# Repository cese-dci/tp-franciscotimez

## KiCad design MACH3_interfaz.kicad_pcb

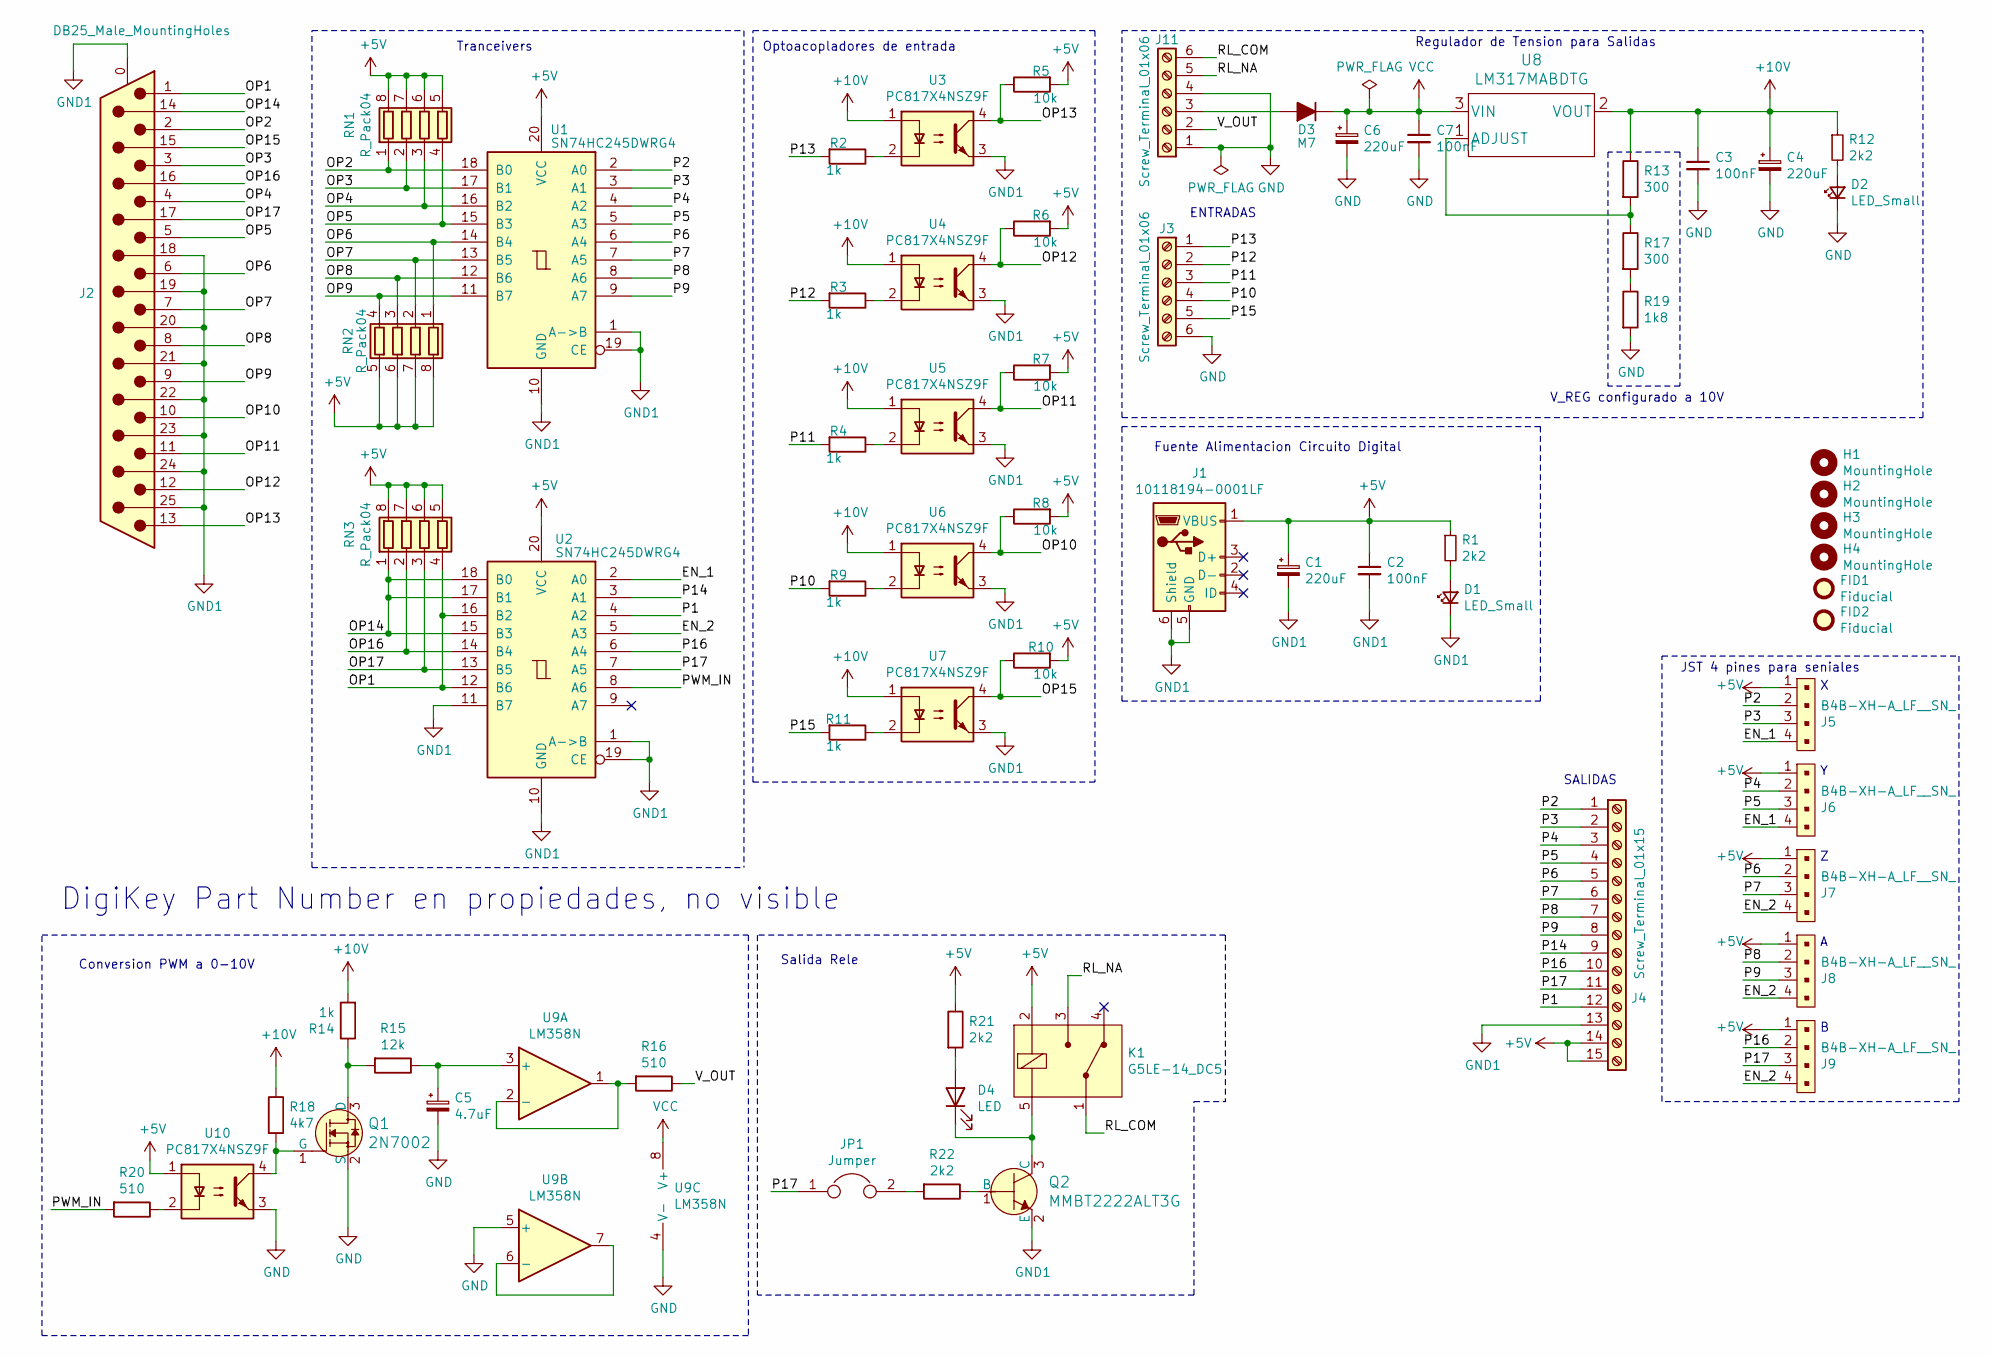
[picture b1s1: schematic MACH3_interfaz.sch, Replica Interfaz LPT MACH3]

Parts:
C1, C4: 220uF; CP_Radial_D6.3mm_P2.50mm
C2, C3, C7: 100nF; C_0805_2012Metric_Pad1.18x1.45mm_HandSolder
C5: 4.7uF; CP_Radial_D5.0mm_P2.00mm
C6: 220uF; CP_Radial_D8.0mm_P3.80mm
D1, D2: LED_Small; LED_0805_2012Metric_Pad1.15x1.40mm_HandSolder
D3: M7; D_SMA_Handsoldering
D4: LED; LED_0805_2012Metric_Pad1.15x1.40mm_HandSolder
FID1, FID2: Fiducial; Fiducial_1mm_Mask3mm
H1, H2, H3, H4: MountingHole; MountingHole_3.2mm_M3
J1: 10118194-0001LF; USB_Micro-B_Amphenol_10118194_Horizontal; DigiKey 609-4618-2-ND - Tape & Reel (TR)
J2: DB25_Male_MountingHoles; DSUB-25_Male_Horizontal_P2.77x2.84mm_EdgePinOffset4.94mm_Ho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
J3, J11: Screw_Terminal_01x06; TerminalBlock_Phoenix_MKDS-1,5-6_1x06_P5.00mm_Horizontal
J4: Screw_Terminal_01x15; TerminalBlock_Phoenix_MKDS-1,5-15_1x15_P5.00mm_Horizontal
J5, J6, J7, J8, J9: B4B-XH-A_LF__SN_; PinHeader_1x4_P2.5mm_Drill1.1mm; MPN B4B-XH-A(LF)(SN); Digi-Key_PN 455-2249-ND
JP1: Jumper; TestPoint_2Pads_Pitch2.54mm_Drill0.8mm
K1: G5LE-14_DC5; Relay_THT_G5LE-14; MPN G5LE-14 DC5; Digi-Key_PN Z1011-ND
Q1: 2N7002; SOT-23-3; MPN 2N7002; Digi-Key_PN 2N7002NCT-ND
Q2: MMBT2222ALT3G; SOT-23-3; MPN MMBT2222ALT3G; Digi-Key_PN MMBT2222ALT3GOSCT-ND
R1, R12, R21, R22: 2k2; R_0805_2012Metric_Pad1.20x1.40mm_HandSolder
R2, R3, R4, R9, R11, R14: 1k; R_0805_2012Metric_Pad1.20x1.40mm_HandSolder
R5, R6, R7, R8, R10: 10k; R_0805_2012Metric_Pad1.20x1.40mm_HandSolder
R13, R17: 300; R_0805_2012Metric_Pad1.20x1.40mm_HandSolder
R15: 12k; R_0805_2012Metric_Pad1.20x1.40mm_HandSolder
R16, R20: 510; R_0805_2012Metric_Pad1.20x1.40mm_HandSolder
R18: 4k7; R_0805_2012Metric_Pad1.20x1.40mm_HandSolder
R19: 1k8; R_0805_2012Metric_Pad1.20x1.40mm_HandSolder
RN1, RN2, RN3: R_Pack04; R_Array_Convex_4x1206
U1, U2: SN74HC245DWRG4; SO-20_12.8x7.5mm_P1.27mm; DigiKey 296-52721-2-ND - Tape & Reel (TR)
U3, U4, U5, U6, U7, U10: PC817X4NSZ9F; DIP-4_W7.62mm; DigiKey PC817X4NSZ9F-ND
U8: LM317MABDTG; TO-252-3_TabPin2; DigiKey LM317MABDTG-ND
U9: LM358N; SOIC-8_3.9x4.9mm_P1.27mm; DigiKey 2156-LM358N-ND

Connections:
+5V: C1.1, C2.1, J1.1 (VBUS), J4.14, J4.15, J5.1, J6.1, J7.1, J8.1, J9.1, K1.2 (COIL), R1.1, R5.2, R6.2, R7.2, R8.2, R10.2, R21.1, RN1.5 (R4.2), RN1.6 (R3.2), RN1.7 (R2.2), RN1.8 (R1.2), RN2.5 (R4.2), RN2.6 (R3.2), RN2.7 (R2.2), RN2.8 (R1.2), RN3.5 (R4.2), RN3.6 (R3.2), RN3.7 (R2.2), RN3.8 (R1.2), U1.20 (VCC), U2.20 (VCC), U10.1
+10V: C3.1, C4.1, R12.1, R13.1, R14.2, R18.1, U3.1, U4.1, U5.1, U6.1, U7.1, U8.2 (VOUT)
/EN_1: J5.4, J6.4, U2.2 (A0)
/EN_2: J7.4, J8.4, J9.4, U2.5 (A3)
/OP1: J2.1, RN3.4 (R4.1), U2.12 (B6), U2.16 (B2)
/OP2: J2.2, RN1.1 (R1.1), U1.18 (B0)
/OP3: J2.3, RN1.2 (R2.1), U1.17 (B1)
/OP4: J2.4, RN1.3 (R3.1), U1.16 (B2)
/OP5: J2.5, RN1.4 (R4.1), U1.15 (B3)
/OP6: J2.6, RN2.1 (R1.1), U1.14 (B4)
/OP7: J2.7, RN2.2 (R2.1), U1.13 (B5)
/OP8: J2.8, RN2.3 (R3.1), U1.12 (B6)
/OP9: J2.9, RN2.4 (R4.1), U1.11 (B7)
/OP10: J2.10, R8.1, U6.4
/OP11: J2.11, R7.1, U5.4
/OP12: J2.12, R6.1, U4.4
/OP13: J2.13, R5.1, U3.4
/OP14: J2.14, RN3.1 (R1.1), U2.15 (B3), U2.17 (B1), U2.18 (B0)
/OP15: J2.15, R10.1, U7.4
/OP16: J2.16, RN3.2 (R2.1), U2.14 (B4)
/OP17: J2.17, RN3.3 (R3.1), U2.13 (B5)
/P1: J4.12, U2.4 (A2)
/P2: J4.1, J5.2, U1.2 (A0)
/P3: J4.2, J5.3, U1.3 (A1)
/P4: J4.3, J6.2, U1.4 (A2)
/P5: J4.4, J6.3, U1.5 (A3)
/P6: J4.5, J7.2, U1.6 (A4)
/P7: J4.6, J7.3, U1.7 (A5)
/P8: J4.7, J8.2, U1.8 (A6)
/P9: J4.8, J8.3, U1.9 (A7)
/P10: J3.4, R9.2
/P11: J3.3, R4.2
/P12: J3.2, R3.2
/P13: J3.1, R2.2
/P14: J4.9, U2.3 (A1)
/P15: J3.5, R11.2
/P16: J4.10, J9.2, U2.6 (A4)
/P17: J4.11, J9.3, JP1.1, U2.7 (A5)
/PWM_IN: R20.2, U2.8 (A6)
/RL_COM: J11.6, K1.1 (COM)
/RL_NA: J11.5, K1.3 (NO)
/V_OUT: J11.2, R16.1
GND: C3.2, C4.2, C5.2, C6.2, C7.2, D2.1 (K), J3.6, J11.1, J11.4, Q1.2 (S), R19.2, U9.4 (V-), U9.5 (+), U10.3
GND1: C1.2, C2.2, D1.1 (K), J1.5 (GND), J1.6 (Shield), J2.0 (PAD), J2.18, J2.19, J2.20, J2.21, J2.22, J2.23, J2.24, J2.25, J4.13, Q2.2 (E), U1.1 (A->B), U1.10 (GND), U1.19 (CE), U2.1 (A->B), U2.10 (GND), U2.11 (B7), U2.19 (CE), U3.3, U4.3, U5.3, U6.3, U7.3
unnamed: C5.1, R15.1, U9.3 (+)
unnamed: D1.2 (A), R1.2
unnamed: D2.2 (A), R12.2
unnamed: D3.2 (A), J11.3
unnamed: D4.1 (K), K1.5 (COIL), Q2.3 (C)
unnamed: D4.2 (A), R21.2
unnamed: JP1.2, R22.2
unnamed: Q1.1 (G), R18.2, U10.4
unnamed: Q1.3 (D), R14.1, R15.2
unnamed: Q2.1 (B), R22.1
unnamed: R2.1, U3.2
unnamed: R3.1, U4.2
unnamed: R4.1, U5.2
unnamed: R9.1, U6.2
unnamed: R11.1, U7.2
unnamed: R13.2, R17.1, U8.1 (ADJUST)
unnamed: R16.2, U9.1, U9.2 (-)
unnamed: R17.2, R19.1
unnamed: R20.1, U10.2
unnamed: U9.6 (-), U9.7
VCC: C6.1, C7.1, D3.1 (K), U8.3 (VIN), U9.8 (V+)

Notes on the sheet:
ENTRADAS
SALIDAS
V_REG configurado a 10V
Fuente Alimentacion Circuito Digital
Regulador de Tension para Salidas
Salida Rele
Conversion PWM a 0-10V
Optoacopladores de entrada
Tranceivers
JST 4 pines para seniales
DigiKey Part Number en propiedades, no visible

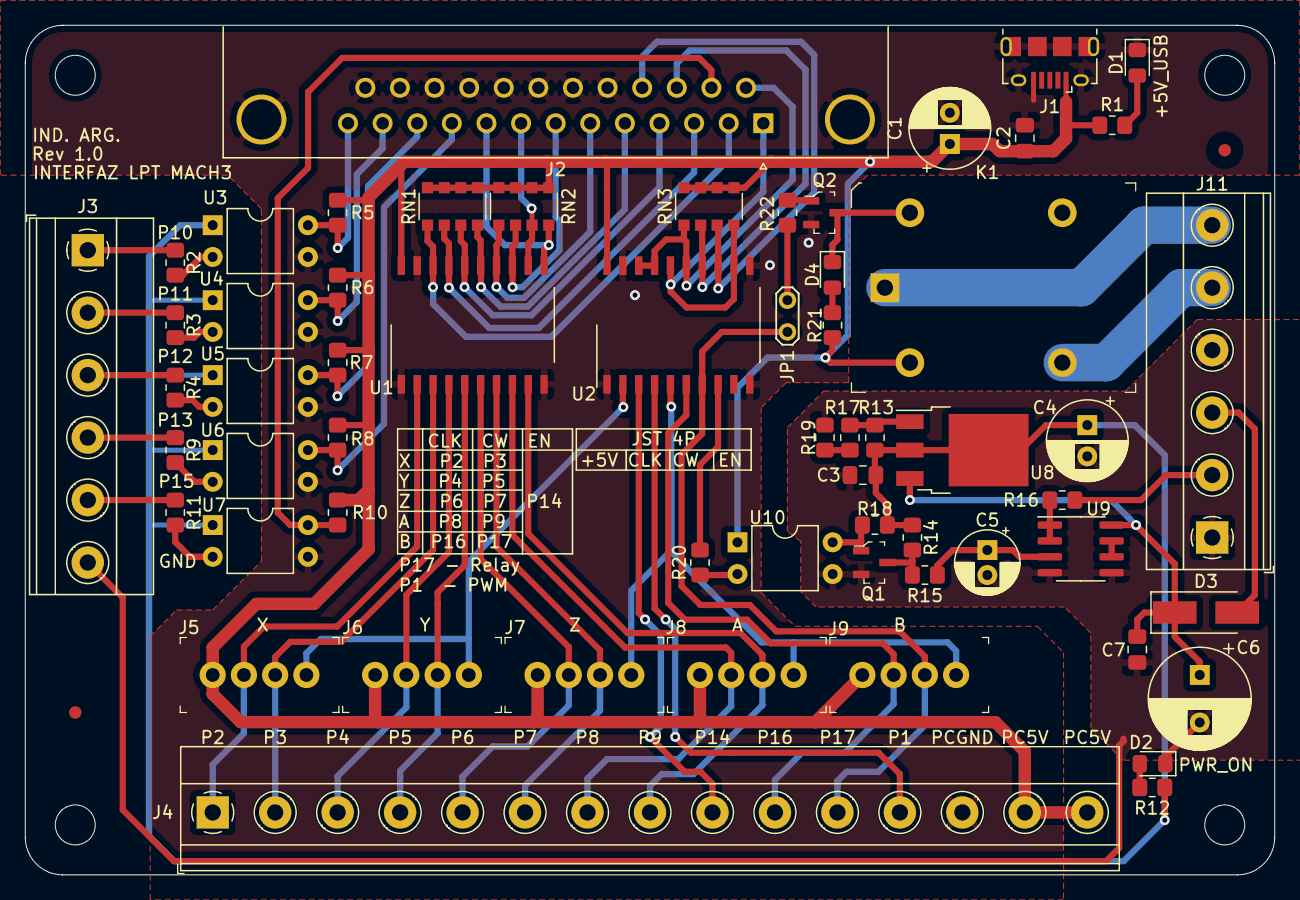
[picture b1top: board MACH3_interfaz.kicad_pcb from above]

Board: 2 copper layers, 100.0 x 68.0 mm, 66 parts (0 on the bottom side), 65 nets.

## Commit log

2021-04-06 Primer commit
2021-04-17 Listo para revison de esquematico
2021-04-17 Para correccion Docente Eschema, Companiero PCB
2021-04-27 Listo para revision final

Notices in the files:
MACH3_interfaz.sch:
https://ohwr.org/project/cernohl/wikis/Documents/CERN-OHL-version-2
